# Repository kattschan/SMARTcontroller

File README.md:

# SMARTcontroller
SMART RS232 -> ESP32 controller
This takes an RS232 male port off of a SMART MX board, runs it through a MAX2323 UART converter, and connects it to an ESP32, where it will be connectable to with a phone, bluetooth peripheral, dedicated controller, etc.
Costs are $99.68 for the cheapest shipping and doing some hand soldering with some more complex parts installed by JLCPCB.

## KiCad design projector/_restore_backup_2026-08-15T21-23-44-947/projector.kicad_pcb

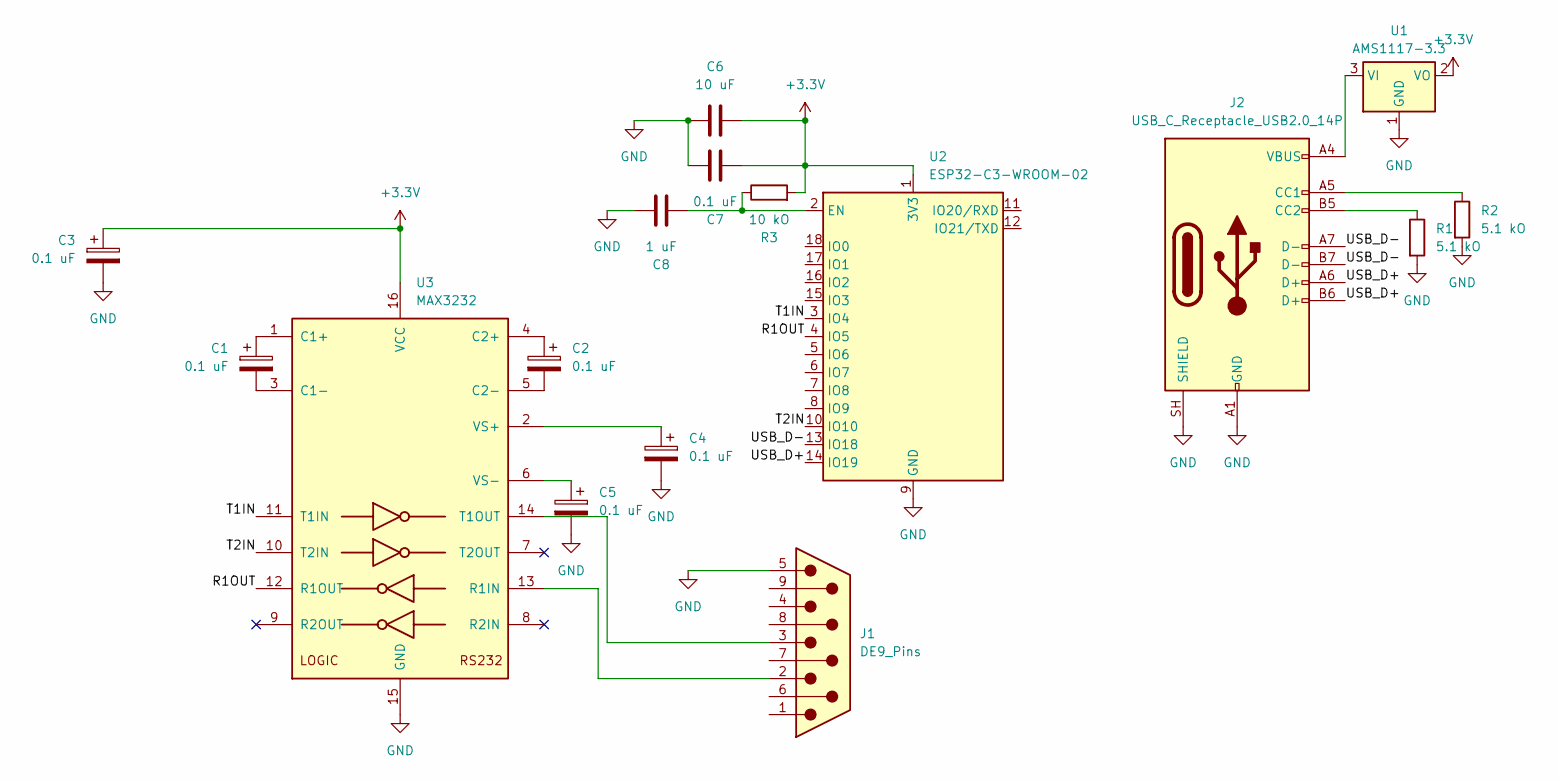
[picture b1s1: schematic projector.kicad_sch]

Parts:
C1, C2, C3, C4, C5, C7: 0.1 uF; CP_Radial_D5.0mm_P2.50mm
C6: 10 uF; CP_Radial_D5.0mm_P2.50mm
C8: 1 uF; CP_Radial_D5.0mm_P2.50mm
J1: DE9_Pins; DSUB-TH_Z-SUBDRAM602A002
J2: USB_C_Receptacle_USB2.0_14P; USB_C_Receptacle_HRO_TYPE-C-31-M-12
R1, R2: 5.1 kO; C_0402_1005Metric
R3: 10 kO; R_Axial_DIN0411_L9.9mm_D3.6mm_P15.24mm_Horizontal
U1: AMS1117-3.3; SOT-223-3_TabPin2
U2: ESP32-C3-WROOM-02
U3: MAX3232; TSSOP-16_L5.0-W4.4-P0.65-LS6.4-BL

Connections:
+3.3V: C3.1, C6.2, C7.2, R3.2, U1.2 (VO), U2.1 (3V3), U3.16 (VCC)
/R1OUT: U2.4 (IO5), U3.12 (R1OUT)
/T1IN: U2.3 (IO4), U3.11 (T1IN)
/T2IN: U2.10 (IO10), U3.10 (T2IN)
/USB_D+: J2.A6 (D+), J2.B6 (D+), U2.14 (IO19)
/USB_D-: J2.A7 (D-), J2.B7 (D-), U2.13 (IO18)
GND: C3.2, C4.2, C5.2, C6.1, C7.1, C8.1, J1.5, J2.A1 (GND), J2.A12 (GND), J2.B1 (GND), J2.B12 (GND), J2.SH (SHIELD), R1.2, R2.2, U1.1 (GND), U2.9 (GND), U2.19 (GND), U3.15 (GND)
unnamed: J2.A5 (CC1), R2.1
unnamed: J2.B5 (CC2), R1.1
unnamed: J2.A4 (VBUS), J2.A9 (VBUS), J2.B4 (VBUS), J2.B9 (VBUS), U1.3 (VI)
unnamed: C8.2, R3.1, U2.2 (EN)
unnamed: C1.1, U3.1 (C1+)
unnamed: C1.2, U3.3 (C1-)
unnamed: C2.1, U3.4 (C2+)
unnamed: C2.2, U3.5 (C2-)
unnamed: J1.2, U3.13 (R1IN)
unnamed: J1.3, U3.14 (T1OUT)
unnamed: C4.1, U3.2 (VS+)
unnamed: C5.1, U3.6 (VS-)

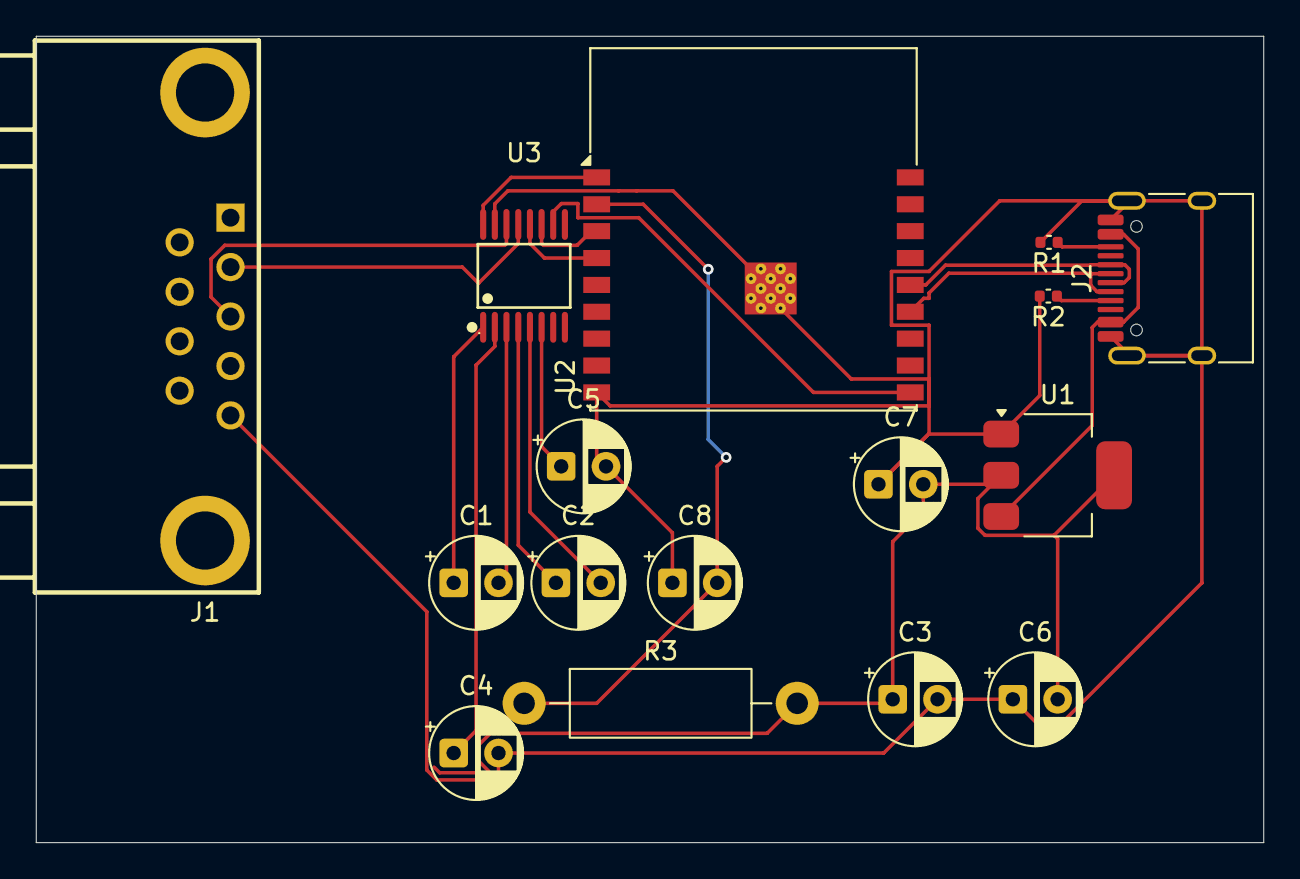
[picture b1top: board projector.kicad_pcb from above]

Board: 2 copper layers, 68.5 x 45.0 mm, 16 parts (0 on the bottom side), 19 nets.
